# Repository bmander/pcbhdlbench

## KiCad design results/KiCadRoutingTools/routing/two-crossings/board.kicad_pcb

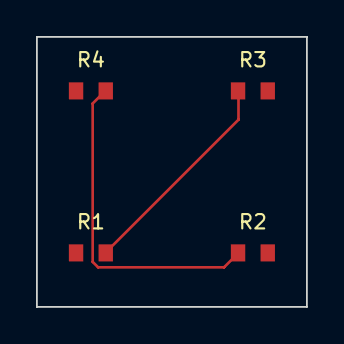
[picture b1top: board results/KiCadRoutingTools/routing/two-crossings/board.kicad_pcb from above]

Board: 2 copper layers, 15.0 x 15.0 mm, 4 parts (0 on the bottom side), 2 nets.

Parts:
R1, R2, R3, R4: R_0603

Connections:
A: R1.2, R3.1
B: R2.1, R4.2

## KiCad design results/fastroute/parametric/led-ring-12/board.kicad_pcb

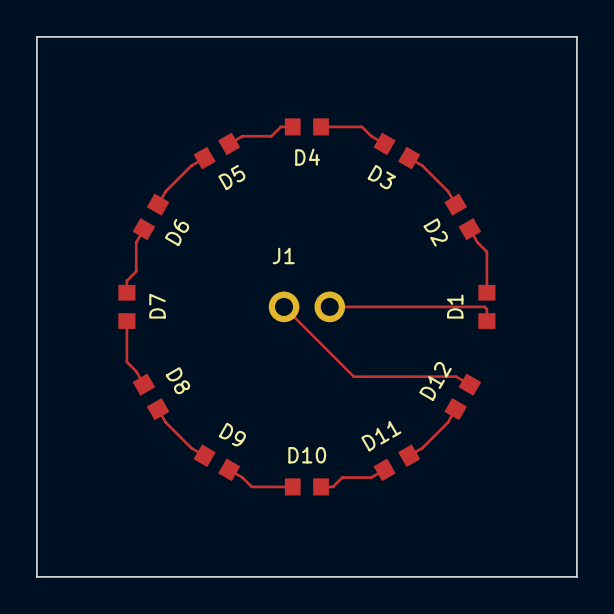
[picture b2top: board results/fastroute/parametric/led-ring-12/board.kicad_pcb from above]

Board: 2 copper layers, 30.0 x 30.0 mm, 13 parts (0 on the bottom side), 13 nets.

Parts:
D1, D2, D3, D4, D5, D6, D7, D8, D9, D10, D11, D12: LED_0603
J1: HDR_1x2_2.54

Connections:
GND: D1.K, J1.2
L1: D1.A, D2.K
L2: D2.A, D3.K
L3: D3.A, D4.K
L4: D4.A, D5.K
L5: D5.A, D6.K
L6: D6.A, D7.K
L7: D7.A, D8.K
L8: D8.A, D9.K
L9: D9.A, D10.K
L10: D10.A, D11.K
L11: D11.A, D12.K
VIN: D12.A, J1.1
